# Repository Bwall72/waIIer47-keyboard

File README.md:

# WaIIer47 Mechanical Keyboard
Custom design 47 key ortholinear keyboard with PCB, and Atmega32u4 Microcontroller

## Images

Revision 2 Green, Revision 1 White, Back top, Front bottom

# Bill Of Materials

* See [BOM.md](./BOM.md)
* The total cost for a Rev 2 PCB keybarod is:

| Component | Unit Price | Units | Total |
| --------- | ---------- | ----- | ----- |
| Capacitor 22 pF | \$0.043  | 2 | \$0.086  |
| Capacitor 0.1 $\mu$F | \$0.0216  | 5 | \$0.108  |
| Capacitor 1.0 $\mu$F | \$0.055 | 1 | \$0.055 |
| Diode | \$.02446 | 47 | \$1.223 |
| LED | \$0.159 | 1 | \$0.159 |
| USB-C Receptacle | \$1.37 | 1 | \$1.37 |
| Kalih Speed Copper Key Switch | \$0.538 | 47 | \$25.286 |
| Resistor 10 k$\Omega$ | \$0.0071 | 2 | \$0.0142 |
| Resistor 22 $\Omega$ | \$0.0071 | 2 | \$0.0142 |
| Resistor 5.1 k$\Omega$ | \$0.0071 | 2 | \$0.0142 |
| Resistor 220 $\Omega$ | \$0.0071 | 1 | \$0.0071 |
| Push Button Switch | \$0.59 | 1 | \$0.59 |
| Atmega32U4 | \$4.08 | 1 | \$4.08 |
| Crystal Oscillator | \$0.36 | 1 | \$0.36 |
| PCB | \$2.08 | 2 | \$2.08 |
| M3 Screws | \$0.033 | 7 | \$0.233
| M3 Standoff | \$0.033 | 7 | \$0.233
| Total ||| \$35.89

>Notes
>
>* Shipping costs are excluded from the BOM
>* Currently, I am reusing keycaps, so those are not included in the BOM
>  * I am part of the group buy for [KAT Mizu Keycaps](https://old.reddit.com/r/mechmarket/comments/i6aaga/ic_kat_mizu_coming_september_1st/), which would add \$64.44 to the total
>* Kailh Speed Copper are my favorite switches, but they cannot be recomended for this keyboard. They are missing the pins to be used in a plateless keyboard like this one.

# PCB Tutorial
Designing a custom mechanical keyboard PCB using KiCad. The following was based on [Ruiqi Mao's Tutorial](https://github.com/ruiqimao/keyboard-pcb-guide)

## Download Kicad and Install the Mechanical Keyboard Libraries

* Download and install Kicad from https://kicad-pcb.org/
  * During installation, choose to download Kicad's default libraries
* Clone the following two repositories (or download zip and extract):
  * `keyboard_parts.pretty` from https://github.com/tmk/keyboard_parts.pretty
  * `keebs.pretty` from https://github.com/egladman/keebs.pretty
  * `Type-C.pretty` from https://github.com/ai03-2725/Type-C.pretty
  * `kicad_lib_tmk`.lib https://github.com/tmk/kicad_lib_tmk

* Open `Kicad` > `Preferences` > `Manage Footprint Libraries`
  * In the `Global Libraries` tab, press the folder icon to `Add existing library to table`
  * Navigate to where you cloned the the libraries, click on the `keebs.pretty` and press `OK`
    * Do the same for `keyboard_parts.pretty` and `Type-C.pretty`
  * If done successfully, you should see the following in the `Global Libraries` tab:

* Back in the Kicad Menu, `Preferences` > `Mange Symbol Libraries`
  * In the `Global Libraries` tab, press the folder icon to `Add existing library to table`
  * Navigate to where you cloned `kicad_lib_tmk` and select `keyboard_parts.lib`
  * Navigate to `Type-C.pretty` and select `Type-C.lib`
  * If done successfully, you should see the following:

## Creating The Schematic File

* In Kicad: `file` > `New` > `New Project`
  * Create a new Folder for the project, and give a name for the project (I am using `tutorial_keyboard`)
  * Press `Save`
  * On the left side, you should now see 3 files:
    * `tutorial_keyboard.kicad_pcb`: The PCB file
    * `tutorial_keyboard.pro`: The project file, we will not be using this
    * `tutorial_keyboard.sch`: The schematic file

* Click on the `Schematic Layout Editor` button
* Because this schematic will be large, increase the paper size by going to `file` > `Page Settings...` then selecting the `C` page size

## Placing Components on the Schematic

* To place a part, press the `Place symbol` button on the right side
* For the microcontroller:
  * `Place symbol` and click on the page > expand `keybord_parts` > select `ATMEGA32U4` > press `OK` > Click on the sheet to place the component
  * You should now see the component placed on your page with the label U?

* Place the following components as required by the [datasheet](http://ww1.microchip.com/downloads/en/devicedoc/atmel-7766-8-bit-avr-atmega16u4-32u4_datasheet.pdf)
  * A 10 k$\Omega$ resustor near `HWB/PE2`
    * `Place symbol` > `keyboard_parts` > `R` > `Ok`
      * Press `r` before placing the component, or while hovering over the component after placing to rotate it
      * Hover over it and press `e` to `Edit Value Field`
      * Change the `Text` field to say `10k`
    
  * A 1 $\mu$F capacitor on `UCap`
    * `place symbol` > `keyboard_parts` > `C` > `Ok`
    * Change the its value to `1uF`

* Connect `Vcc` and `GND`
  * On the right side, slect `Place power port` > click on the page
  * Expand the `power` library and select > `VCC` > `Ok`
  * Place the VCC flag near `AVCC`
    * On the right, click the `Place wire` icon
    * Click at the empty circle on `AVCC` and make a connection to the `VCC` flag
    
    * Repeat for:
      | Pin | Name   |
      |-----|--------|
      | 2   | `UVcc` |
      | 7   | `VBus` |
      | 14  | `VCC`  |
      | 24  | `AVcc` |
      | 34  | `VCC`  |
      | 44  | `AVcc` |
    * Make sure there are 6 total connections to `VCC`
    * Individual connections to `VCC` in the schematic do not need to be connected together
    * Connect `VCC` to a power flag
      * `Place symbol` > Search for `PWR_FLAG` > `PWR_FLAG`
      * Connect the `PWR_FLAG` to `VCC`
      
  * `Place power port` > `GND` (`Power flag, ground` from the `s`power` library)
    * Create a connection to `GND` on the following pins:
      | Pin | Name   |
      | --- | ------ |
      | 5   | `UGND` |
      | 15  | `GND`  |
      | 23  | `GND`  |
      | 35  | `GND`  |
      | 43  | `GND`  |
    * Additionally, connect the other end of the capacitor and resistor to `GND`
    * Make sure there are 5 connections to `GND`

* If there are any overlapping components or labels, press `m` over the component/label to move it somewhere else
  * You will have to remake any connections
* Reset Circuit
  * The following allows for a manual reset button that (If you do not want a reset button, connect `RESET` to `VCC`)
  * Move to an open part of the page
  * `Place symbol` > `keyboard_parts` > `SW_PUSH`
  * We want the voltage supplied to the reset pin to be `High (5V)` normally, and ground when pushed to reset the microcontroller
  * Connect the left side to `GND`
  * Create a connection between `VCC` -> 10 k$\Omega$ resistor -> switch-s right pin
  
  * Place a flag on the right side:
    * In the right menu: `Place net label`
    * Give it the name `Reset`
    * Connect it to the wire on the right side
    * Place a net label with the name `Reset` on the `RESET` pin (pin 13) of the microcontroller
    * The reset circuit is now connected to the microcontroller
    
* USB Type-C Circuit
  * This keyboard will connect to a computer using a USB-C connector in USB 2.0 Mode
  * `Place symbol` > `Connector` > `USB_C_Receptacle_USB2.0`
  * Make the following connections

  | Receptacle Port | Connection |
  | --------------- | ---------- |
  | `VBUS` | `VCC` |
  | `CC1` | 5.1 k$\Omega$ resistor -> `GND` |
  | `CC2` | 5.1 k$\Omega$ resistor -> `GND` |
  | `D-` | Connect both `D-` pins through a 22 $\Omega$  resistor to a net called `D-` |
  | `D+` | Connect both `D+` pins through a 22 $\Omega$ resistor to a net called `D+` |
  | `SBU1` | Leave unconnected |
  | `SBU2` | Leave unconnected |
  | `GND` | `GND` |
  | `SHIELD` | `GND` |
  
  * On the microcontroller, connect `D-` (pin 3) to the `D-` net and `D+` (pin 4) to the `D+` net

* Crystal Oscillator Circuit
  * The following circuit is required for the microcontroller to function as a USB device
  * `Place symbol` > `keyboard_parts` > `XTAL`
  * Connect a 22 pF capacitor to both ends of the `XTAL` with the other side going off to `GND`
  * Connect one side of the `XTAL` to a net called `xtal1` and the other to a net called `xtal2`
  * Connect the `xtal1` net to `XTAL1` (pin 16) and `xtal2` to `XTAL2` (pin 17) on the microcontroller

* Placing the keys
  * The following circuit is used for all the keys:
  
  * `Place symbol` > `keyboard_parts` > `KEYSW`
  * `Place symbol` > `keyboard_parts` > `D`
  * Connect the `2 pin` on the `KEYSW` on to the 2 pin on the diode **Orientation on the diode is extremely important**
  * For an 47 key ortholinear keyboard, copy and paste this circuit 46 times in rows of 12 (besides the third row which should have 11 keys)
  * Connect all the pin 1's on the switch on the same row
  * Connect all the pin 1's on the diode to the next pin 2 on the switch in the columns
  
  * Connect the bottom row diodes together
  
  * Create a net on the each of the vertical wire segments in the top row named `col0` to `col11`
  * Create a net on the the left most switch of each row labeled `row0` to `row3`

  * Connect each of the row and col nets to a GPIO pin on the microcontroller (`PAX`, `PBX`, `PCX`, or `PDX`) these can be changed later to make it easier to route the PCB
  
* Bypass Capacitors
  * Bypass capacitors are placed between all `VCC` nets and `GND`, watch this [video to learn more](https://www.youtube.com/watch?v=BcJ6UdDx1vg)
  * There are 6 connections that will use bypass capacitors
  * Create the following circuit using 0.1 $\mu$ capacitors
  
* Mark all unconnected ports
  * In the right menu, click `Place no connection flag`
  * Place the symbol over all unused ports on the microcontroller and on `SBU1` and `SBU2` on the USB C receptacle
  
* Annotate the schematic to give components names
  * `Tools` > `Annotate Schematic`
  * Keep all default settings
  * Press `Annotate`
  * `Close`
* Run a Design Rules Check to make sure there are no errors in the circuit
  * `Perform electrical rules check` > `Run`
  * Fix any errors that occur, if there are only errors for your `VCC` or `GND` not being driven, you can move on

## Assigning Footprints

* Assigning footprints tell the PCB software what size to make all of your components. Additionally you will buy components based off the size of their footprint. For most components we will use the `0805` surface mount package. If you do not feel comfortable surface mounting components, you will have to heavily modify the PCB layout.
* `Tools` > `Assign Footprints...`
  | Components | Library | Footprint |
  | ---------- | ------- | --------- |
  | All Capacitors | `Capacitor_SMD` | `Capacitor_SMD:C_0805_2012Metric` |
  | All Diodes | `Diode_SMD` | `Diode_SMD:D_0805_2012Metric` |
  | USB C Receptacle | `Type-C` | `Type-C:USB_C_GCT_USB4085` |
  | All `KEYSW` **EXCEPT FOR THE SPACE BAR** | `keebs` | `keebs:Mx_Alps_100` |
  | Space Bar (sixth key in on the bottom row) | `keebs` | `keebs:Mx_Alps_200` |
  | All Resistors | `Resistor_SMD` | `Resistor_SMD:R_0805_2012Metric` |
  | `SW_PUSH` | `Button_Switch_SMD` | `Button_Switch_SMD:SW_SPST_TL3342` |
  | `ATMEGA32U4` | `Package_QFP` | `Package_QFP:TQFP-44_10x10mm_P0.8mm` |
  | `XTAL` | `keyboard_parts` | `keyboard_parts:XTAL_HC_49_TH`

  * Press `OK`

## Creating the PCB

### Set the Grid Size

* Click the `Grid` dropdown menu on the top
* `Edit User Grid`
* Set `Size X` and `Size Y` to `0.254`

### Importing From the Schematic

* Close the schematic and open `PCB Layout Editor`
* `Tools` > `Update PCB from Schematic`
* Click Anywhere to Place all the components
* Click `Layers Manager` > `Items` > Uncheck the box next to `Ratsnest`
  * This will be helpful when routing the PCB, but it is not now

### Organizing your components

* Arrange the keys in the same order as your circuit
* The easiest way I found to do this is to use `ctrl + f` to search for the key annotations
* I like to leave one _grid snap_ gap between each key, make sure all keys are evenly spaced on the grid
* There should be a visible `+` sign between all groups for 4 adjacent keys

> Follow the annotations from your schematic to put the keys in the correct order

### Place the Other Parts

* Because this keyboard mostly uses surface mount components, they will mostly go on the back to hide them
* To place a component on the back, click on the footprint and press `f`
  * The text for the label should be backwards and in purple
* Flip all diodes to the back, and align them onto their key switch
* Place the diode on the lower part of the key switch (opposite of the gold)

* Turning on `ratsnest` may be helpful for this part
* Arrange the other parts on the back above the key switches
  * All the components in the schematic that are near the microcontroller should go near the microcontroller
  * 5 bypass capacitors should go near the microcontroller with the other going near the USB-C receptacle
* The crystal should go on the back as close as possible to the microcontroller pins it connects to
* The Type-C connector should go on the front, it will be the highest component on the PCB
* The switch can go on the front or back based on preference, I put it on the front

### Adjust your circuit

* With the `ratsnest` turned on, move the location of rows and cols on your microcontroller to reduce the number of ratsnests that overlap
* After making a change, `Tools` > `Update PCB From Schematic`

### Set the Track Width

* I use [JLCPCB](https://jlcpcb.com/) to manufacture my PCBs, their minimum trace width is 5 mil (0.127 mm) with the same minimum spacing

* The default .254 mm width does not need to be changed, but you can go down to .2 mm to have smaller traces

### Making connections

* To make a connection, use the bar on the right to select a layer
  * `F.CU` for components on the front
  * `B.CU` for components on the back
* You must select the layer of the starting component to make a connection
* With the correct layer selected, press `Route tracks`
* Connect all components, but do not connect any `GND` nets, those will all be taken care of in the end

* To make connections easier, click on the footprint and press `R` to rotate the component if that makes it easier
* I recommend breaking out all the pins of the microcontroller before worrying about connecting the microcontroller to components
* If traces are going to overlap, press `v` to insert a `via` between the front and the back to switch layers

### Create the Remaining Connections

Connect the diodes for all keys in the same row

Connect the switches in the same column

Break out connections from the USB-C receptacle

### Add Mounting Holes

* This desing suspends the PCB from standoffs, to use them, m3 screw holes are added to the PCB
* `Place` > `Footprint` > `MountingHole_3.2mm_M3`
* I personally put 3 screw holes on each side and one in the middle
  * Adding more holes can make the PCB flex less

### Creating an outline for the PCB

* Select the `Edge.Cuts` layer
* Select the `Add graphic lines` tool
* Draw a **fully connected** rectangle around all your components
* The USB-C connector should be on the outer limits of the PCB on the top, and the screw holes should be the limit on the sides
* The smaller the PCB, the cheeper it will be to fabricate

* After creating the outline, try opening `View` > `3D Viewer`
* If you see the folowing error, look for any missing connections in your edge cuts or extra lines

* Once you fix all the errors, you should be able to view a 3D rendering of the PCB

### Adding a Ground Plane

* In the previous steps, no connections were made to ground, we will resolve them all now
* On the right side, select the `Add filled zones` tool on the back side and the `GND` net

* Select the top left corner > top right corner > bottom right corner > **double click on the lower left corner**
* You should see:

* By zooming in, you can see connections made to ground nets

* Repeat the process on the top side

> Press the `Do not show filled zones` button on the left side to hide the filled zones

### Run the Design Rules Check

* Press `Perform Design Rules Check` on the top bar
* Select the `Refill all zones before running DRC` > `Run DRC`
* Resolve any errors that show up
* The most common errors are:
  * Missing connections to ground:
    * It is possible that your filled zones cannot get around a trace or component, you may need to add some manual ground connections
  * Traces too close:
    * Re-route the traces to increase the distance between the traces
  * Traces too close to holes in PCB
    * Move the trace
* When there are no design rule check violations, the PCB is complete

## Submitting PCB for Fabrication

### Generate Gerber Files

* [Refer to this page from JLCPCB for instructions](https://support.jlcpcb.com/article/44-how-to-export-kicad-pcb-to-gerber-files)
* `File` > `Plot`
* Select a folder for `Output Directory`
* On the front page, leave all the default settings and press `Plot`
* Press `Generate Drill Files...`
  * Click the `Gerber` option on the left
  * Press `Generate Drill File`

### Submitting to JLCPCB
(Instructions will also be shown for [OSHPARK](https://oshpark.com/), but they are much more expensive for large PCBs)

* Create a `.zip` from the output folder
* Go to [JLCPCB](www.jlcpcb.com)
* Press `QUOTE NOW`
* `Add your gerber file` > Select your `.zip`
* You can leave all the default options unless you want a different color
* Proceeded with checkout, they will verify your that your design complies with their manufacturing process and has all the needed files
* \$10.40 + 16 for Fedex Shipping
* Total time to receive your PCB should be less than two weeks (unless shipping by boat)

### OSHPARK

* PCBs from OSHPARK are more expensive, but higher quality. For large runs, it may make sense to use OSHPARK (you also have to be fine with a purple PCB)
* Go to [wwww.oshpark.com](www.oshpark.com)
* Upload your `.zip`
* I saw that their quote was 5 times as much for 2 fiewer PCBs and did not continue...

# Ordering Components from Digikey

* For this tutorial, the following components are purchased from [Digikey](www.digikey.com)
* Note the quantities needed per the schematic and **BUY MORE THAN YOU NEED**, **A LOT MORE** (I generally buy 5-10 times as many of each component, it is often cheaper to buy at higher quantities)

| Item # | Item | Price | Digikey Link | Data Sheet |
| ------ | ---- | ------| --------| ---------- |
1 | USB C Connector | \$1.37 | [Link](https://www.digikey.com/product-detail/en/gct/USB4085-GF-A/2073-USB4085-GF-ACT-ND/9859733) | [Link](https://media.digikey.com/pdf/Data%20Sheets/GCT%20PDFs/Ionex_USB_Conn_Br.pdf)
2 | Capacitor (22pF) | \$0.043 | [Link](https://www.digikey.com/product-detail/en/w%C3%BCrth-elektronik/885012007012/732-7816-1-ND/5454443) | [Link](https://www.we-online.de/katalog/datasheet/885012007012.pdf)
3 | Capacitor (0.1 $\mu$F) | \$0.0216 | [Link](https://www.digikey.com/product-detail/en/samsung-electro-mechanics/CL21B104KACNNNC/1276-1099-1-ND/3889185) | [Link](https://media.digikey.com/pdf/Data%20Sheets/Samsung%20PDFs/CL21B104KACNNNC_Spec.pdf)
4 | Capacitor (1 $\mu$F) | \$0.055 | [Link](https://www.digikey.com/product-detail/en/samsung-electro-mechanics/CL21B105KOFNNNE/1276-1026-1-ND/3889112) | [Link](https://www.datasheets360.com/pdf/5320303544541785574)
5 | Diode | \$.02446 | [Link](https://www.digikey.com/product-detail/en/nexperia-usa-inc/BAS16GWJ/1727-7320-1-ND/7390571) | [Link](https://assets.nexperia.com/documents/data-sheet/BAS16GW.pdf)
6 | Resistor (10 k$\Omega$) | $0.0071 | [Link](https://www.digikey.com/product-detail/en/stackpole-electronics-inc/RMCF0805JT10K0/RMCF0805JT10K0CT-ND/1942577) | [Link](https://www.seielect.com/catalog/sei-rmcf_rmcp.pdf)
7 | Resistor (22 $\Omega$) | $0.0071 | [Link](https://www.digikey.com/product-detail/en/stackpole-electronics-inc/RMCF0805JT22R0/RMCF0805JT22R0CT-ND/1942533) | [Link](https://www.seielect.com/catalog/sei-rmcf_rmcp.pdf)
8 | Resistor (5.1 k$\Omega$) | $0.0071 | [Link](https://www.digikey.com/product-detail/en/stackpole-electronics-inc/RMCF0805JT5K10/RMCF0805JT5K10CT-ND/1942571) | [Link](https://www.seielect.com/catalog/sei-rmcf_rmcp.pdf)
9 | Switch | $0.59 | [Link](https://www.digikey.com/product-detail/en/e-switch/TL3342F160QG-TR/EG2531CT-ND/379004) | [Link](https://sten-eswitch-13110800-production.s3.amazonaws.com/system/asset/product_line/data_sheet/165/TL3342.pdf)

* To search on your own for components (resistor example):
  * Go to [Digikey](https://www.digikey.com/)
  * `Products` > `Passives` > `Resistors` > `Chip Resistor - Surface Mount`
  * Use the filters to get the correct value resistor
  * Set the `View Prices At` value to 10
    * For most components, I ended up in the 10-100 piece price bracket
    * This will exclude any components that can only be purchased in high quantities
    * Click `More Filters`
    * `Package` > `0805` (based on the assigned footprint)
    * `Apply All`
    * I also recommend deselecting `Include` under `Marketplace Product`
  * `Applied Filters` should show `Package/Case` and `Resistance`

  * In the table, click the `Search Ascending` arrow under `Price` to show the lowest cost components
    * For this keyboard, there really aren't any components where using a more expensive part is worth getting

* Repeat this process for all the other components, or use the products I listed in the table

## Components From Other Sources

* I already owned the crystal oscillators, which is why I use through hole for them
  * [Amazon - uxcell 16.00 MHz crystal oscillator](https://smile.amazon.com/a14073000ux0239-Profile-Crystal-Oscillator-Replacements/dp/B00SWK2HCO)
* [Amazon - Brass M3 Screw and Standoff Kit](https://smile.amazon.com/Csdtylh-Male-Female-Standoff-Stainless-Assortment/dp/B06Y5TJXY1)

### Keyswitches

* I recommend ordering keyswitches from [Mechanicalkeyboards.com](https://mechanicalkeyboards.com/shop/index.php?l=product_list&c=107)
* **MAKE SURE THE SWITCHES YOU CHOOSE SAY PCB MOUNT**
  * I used my favorite switch, Kalih Speed Copper, which is plate mount
  * PCB mounted switches have two additional feet to help alignment
  * Plate mounted switches are very hard to align
  * Do not buy plate mounted switches

**WIP**

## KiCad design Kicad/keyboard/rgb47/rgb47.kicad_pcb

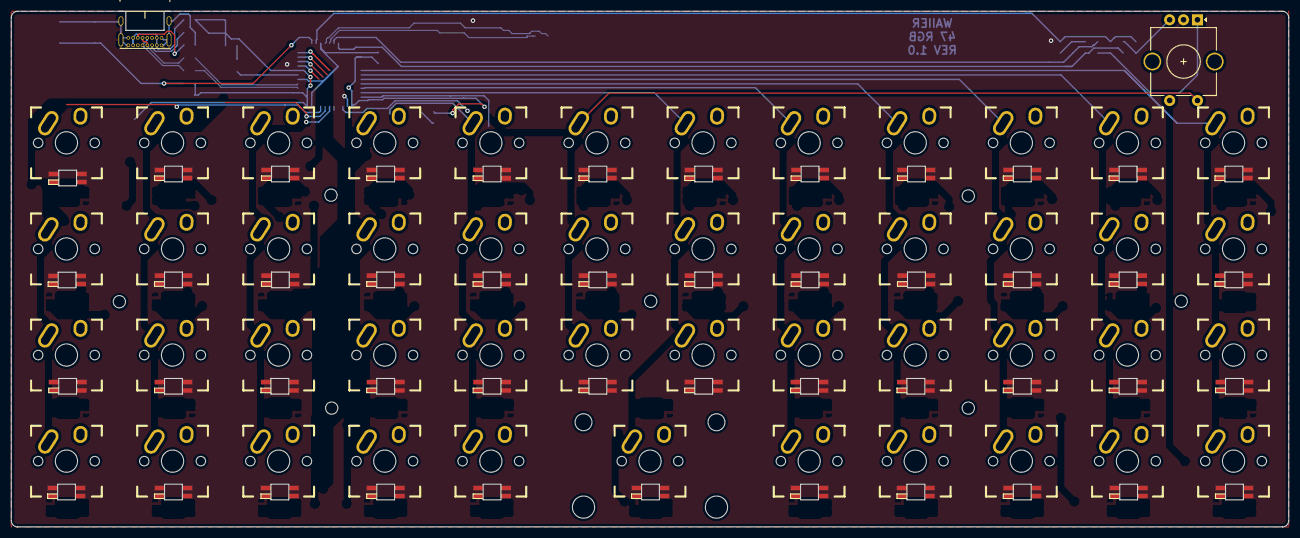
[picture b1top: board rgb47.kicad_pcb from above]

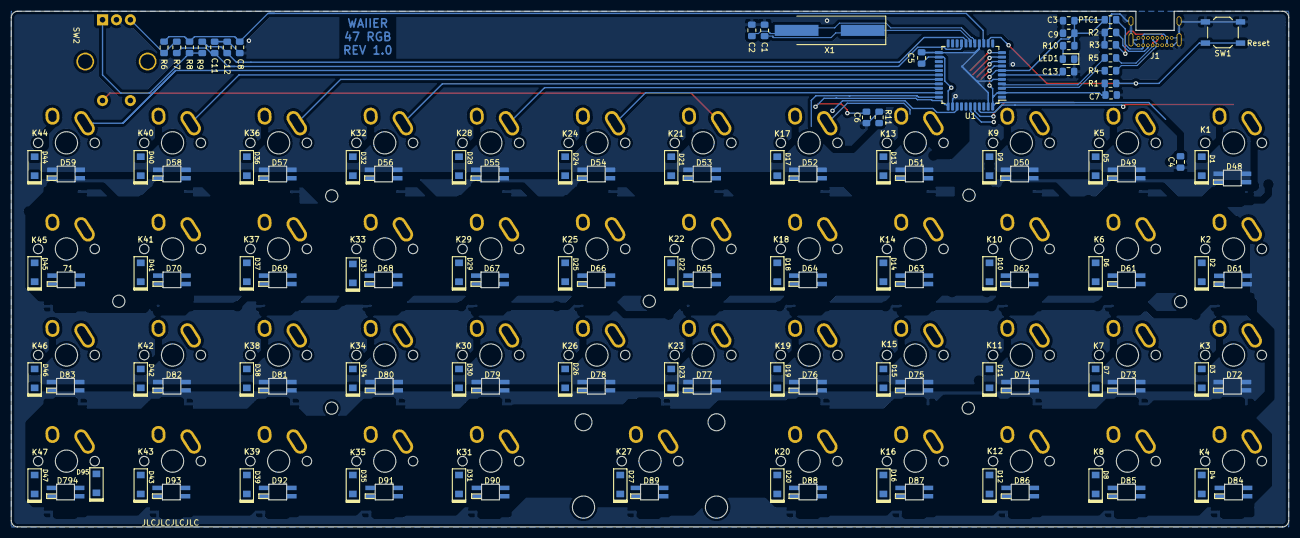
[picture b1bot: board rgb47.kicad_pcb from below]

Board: 2 copper layers, 229.4 x 92.6 mm, 172 parts (76 on the bottom side), 129 nets.

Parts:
71: SK6812; sk6812_mini_E_cuts
C1, C2: 22p; C_0805_2012Metric_Pad1.15x1.40mm_HandSolder
C3, C4, C5, C6, C7, C8, C11, C12: 0.1u; C_0805_2012Metric_Pad1.15x1.40mm_HandSolder
C9: 10u; C_0805_2012Metric_Pad1.15x1.40mm_HandSolder
C13: 1u; C_0805_2012Metric_Pad1.15x1.40mm_HandSolder
D1, D2, D3, D4, D5, D6, D7, D8, D9, D10, D11, D12, D13, D14, D15, D16, D17, D18, D19, D20, D21, D22, D23, D24, D25, D26, D27, D28, D29, D30, D31, D32, D33, D34, D35, D36, D37, D38, D39, D40, D41, D42, D43, D44, D45, D46, D47, D95: D; D_SOD123
D48, D49, D50, D51, D52, D53, D54, D55, D56, D57, D58, D59, D61, D61#2, D62, D63, D64, D65, D66, D67, D68, D69, D70, D72, D73, D74, D75, D76, D77, D78, D79, D80, D81, D82, D83, D84, D85, D86, D87, D88, D89, D90, D91, D92, D93, D794: SK6812; sk6812_mini_E_cuts
J1: USB_C_Receptacle_USB2.0; USB_C_GCT_USB4085
K1, K2, K3, K4, K5, K6, K7, K8, K9, K10, K11, K12, K13, K14, K15, K16, K17, K18, K19, K20, K21, K22, K23, K24, K25, K26, K28, K29, K30, K31, K32, K33, K34, K35, K36, K37, K38, K39, K40, K41, K42, K43, K44, K45, K46, K47: KEYSW; Mx_Alps_100
K27: KEYSW; Mx_Alps_200
LED1: LED; LED_0805_2012Metric_Pad1.15x1.40mm_HandSolder
PTC1: PTC 1.5A; Fuse_0805_2012Metric_Pad1.15x1.40mm_HandSolder
R1, R6, R7, R8, R9, R11: 10k; R_0805_2012Metric_Pad1.15x1.40mm_HandSolder
R2, R3: 5.1k; R_0805_2012Metric_Pad1.15x1.40mm_HandSolder
R4, R5: 22; R_0805_2012Metric_Pad1.15x1.40mm_HandSolder
R10: 220; R_0805_2012Metric_Pad1.15x1.40mm_HandSolder
SW1: SW_PUSH; SW_SPST_TL3342
SW2: Rotary_Encoder_Switch; RotaryEncoder_Alps_EC11E-Switch_Vertical_H20mm_CircularMoun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
U1: ATMEGA32U4; LQFP-44_10x10mm_P0.8mm
X1: XTAL; Crystal_SMD_HC49-SD_HandSoldering

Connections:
5V: 71.3, C3.2, C4.2, C5.2, C6.2, C7.2, C8.2, C9.2, D48.3, D49.3, D50.3, D51.3, D52.3, D53.3, D54.3, D55.3, D56.3, D57.3, D58.3, D59.3, D61.3, D61#2.3, D62.3, D63.3, D64.3, D65.3, D66.3, D67.3, D68.3, D69.3, D70.3, D72.3, D73.3, D74.3, D75.3, D76.3, D77.3, D78.3, D79.3, D80.3, D81.3, D82.3, D83.3, D84.3, D85.3, D86.3, D87.3, D88.3, D89.3, D90.3, D91.3, D92.3, D93.3, D794.1, PTC1.2, R1.1, R6.2, R8.2, R10.1, U1.2, U1.7, U1.14, U1.24, U1.34, U1.44
/COL0: K1.1, K2.1, K3.1, K4.1, U1.41
/COL1: K5.1, K6.1, K7.1, K8.1, U1.40
/COL2: K9.1, K10.1, K11.1, K12.1, U1.39
/COL3: K13.1, K14.1, K15.1, K16.1, U1.38
/COL4: K17.1, K18.1, K19.1, K20.1, U1.37
/COL5: K21.1, K22.1, K23.1, SW2.S2, U1.36
/COL6: K24.1, K25.1, K26.1, K27.1, U1.32
/COL7: K28.1, K29.1, K30.1, K31.1, U1.31
/COL8: K32.1, K33.1, K34.1, K35.1, U1.30
/COL9: K36.1, K37.1, K38.1, K39.1, U1.29
/COL10: K40.1, K41.1, K42.1, K43.1, U1.28
/COL11: K44.1, K45.1, K46.1, K47.1, U1.27
/D+: R5.1, U1.4
/D-: R4.1, U1.3
/ENCODER_A: R8.1, R9.2, SW2.A
/ENCODER_AOUT: C12.2, R9.1, U1.18
/ENCODER_B: R6.1, R7.2, SW2.B
/ENCODER_BOUT: C11.2, R7.1, U1.19
/ENCODER_S1: D95.2, SW2.S1
/RESET: R1.2, SW1.1, U1.13
/RGB: D48.2, U1.1
/ROW0: D1.1, D5.1, D9.1, D13.1, D17.1, D21.1, D24.1, D28.1, D32.1, D36.1, D40.1, D44.1, U1.8
/ROW1: D2.1, D6.1, D10.1, D14.1, D18.1, D22.1, D25.1, D29.1, D33.1, D37.1, D41.1, D45.1, U1.9
/ROW2: D3.1, D7.1, D11.1, D15.1, D19.1, D23.1, D26.1, D30.1, D34.1, D38.1, D42.1, D46.1, U1.10
/ROW3: D4.1, D8.1, D12.1, D16.1, D20.1, D27.1, D31.1, D35.1, D39.1, D43.1, D47.1, D95.1, U1.11
/XTAL_N: C2.2, U1.16, X1.2
/XTAL_P: C1.2, U1.17, X1.1
GND: 71.1, C1.1, C2.1, C3.1, C4.1, C5.1, C6.1, C7.1, C8.1, C9.1, C11.1, C12.1, C13.2, D48.1, D49.1, D50.1, D51.1, D52.1, D53.1, D54.1, D55.1, D56.1, D57.1, D58.1, D59.1, D61.1, D61#2.1, D62.1, D63.1, D64.1, D65.1, D66.1, D67.1, D68.1, D69.1, D70.1, D72.1, D73.1, D74.1, D75.1, D76.1, D77.1, D78.1, D79.1, D80.1, D81.1, D82.1, D83.1, D84.1, D85.1, D86.1, D87.1, D88.1, D89.1, D90.1, D91.1, D92.1, D93.1, D794.3, J1.A1, J1.A12, J1.B1, J1.B12, J1.S1, LED1.1, R2.1, R3.1, R11.1, SW1.2, SW2.C, U1.5, U1.15, U1.23, U1.35, U1.43
unnamed: C13.1, U1.6
unnamed: D1.2, K1.2
unnamed: D2.2, K2.2
unnamed: D3.2, K3.2
unnamed: D4.2, K4.2
unnamed: D5.2, K5.2
unnamed: D6.2, K6.2
unnamed: D7.2, K7.2
unnamed: D8.2, K8.2
unnamed: D9.2, K9.2
unnamed: D10.2, K10.2
unnamed: D11.2, K11.2
unnamed: D12.2, K12.2
unnamed: D13.2, K13.2
unnamed: D14.2, K14.2
unnamed: D15.2, K15.2
unnamed: D16.2, K16.2
unnamed: D17.2, K17.2
unnamed: D18.2, K18.2
unnamed: D19.2, K19.2
unnamed: D20.2, K20.2
unnamed: D21.2, K21.2
unnamed: D22.2, K22.2
unnamed: D23.2, K23.2
unnamed: D24.2, K24.2
unnamed: D25.2, K25.2
unnamed: D26.2, K26.2
unnamed: D27.2, K27.2
unnamed: D28.2, K28.2
unnamed: D29.2, K29.2
unnamed: D30.2, K30.2
unnamed: D31.2, K31.2
unnamed: D32.2, K32.2
unnamed: D33.2, K33.2
unnamed: D34.2, K34.2
unnamed: D35.2, K35.2
unnamed: D36.2, K36.2
unnamed: D37.2, K37.2
unnamed: D38.2, K38.2
unnamed: D39.2, K39.2
unnamed: D40.2, K40.2
unnamed: D41.2, K41.2
unnamed: D42.2, K42.2
unnamed: D43.2, K43.2
unnamed: D44.2, K44.2
unnamed: D45.2, K45.2
unnamed: D46.2, K46.2
unnamed: D47.2, K47.2
unnamed: D48.4, D49.2
unnamed: D49.4, D50.2
unnamed: D50.4, D93.2
unnamed: D51.2, D93.4
unnamed: D51.4, D52.2
unnamed: D52.4, D53.2
unnamed: D53.4, D54.2
unnamed: D54.4, D55.2
unnamed: D55.4, D56.2
unnamed: D56.4, D57.2
unnamed: D57.4, D58.2
unnamed: D58.4, D70.2
unnamed: D59.2, D61.4
unnamed: 71.2, D59.4
unnamed: D61.2, D61#2.4
unnamed: D61#2.2, D62.4
unnamed: D62.2, D63.4
unnamed: D63.2, D64.4
unnamed: D64.2, D65.4
unnamed: D65.2, D66.4
unnamed: D66.2, D67.4
unnamed: D67.2, D68.4
unnamed: D68.2, D69.4
unnamed: D69.2, D70.4
unnamed: 71.4, D72.2
unnamed: D72.4, D73.2
unnamed: D73.4, D74.2
unnamed: D74.4, D794.4
unnamed: D75.2, D794.2
unnamed: D75.4, D76.2
unnamed: D76.4, D77.2
unnamed: D77.4, D78.2
unnamed: D78.4, D79.2
unnamed: D79.4, D80.2
unnamed: D80.4, D81.2
unnamed: D82.2, D83.4
unnamed: D83.2, D84.4
unnamed: D84.2, D85.4
unnamed: D85.2, D86.4
unnamed: D86.2, D87.4
unnamed: D87.2, D88.4
unnamed: D88.2, D89.4
unnamed: D89.2, D90.4
unnamed: D90.2, D91.4
unnamed: D91.2, D92.4
unnamed: J1.A5, R2.2
unnamed: J1.A6, J1.B6, R5.2
unnamed: J1.A7, J1.B7, R4.2
unnamed: J1.B5, R3.2
unnamed: LED1.2, R10.2
unnamed: R11.2, U1.33
VCC: J1.A4, J1.A9, J1.B4, J1.B9, PTC1.1

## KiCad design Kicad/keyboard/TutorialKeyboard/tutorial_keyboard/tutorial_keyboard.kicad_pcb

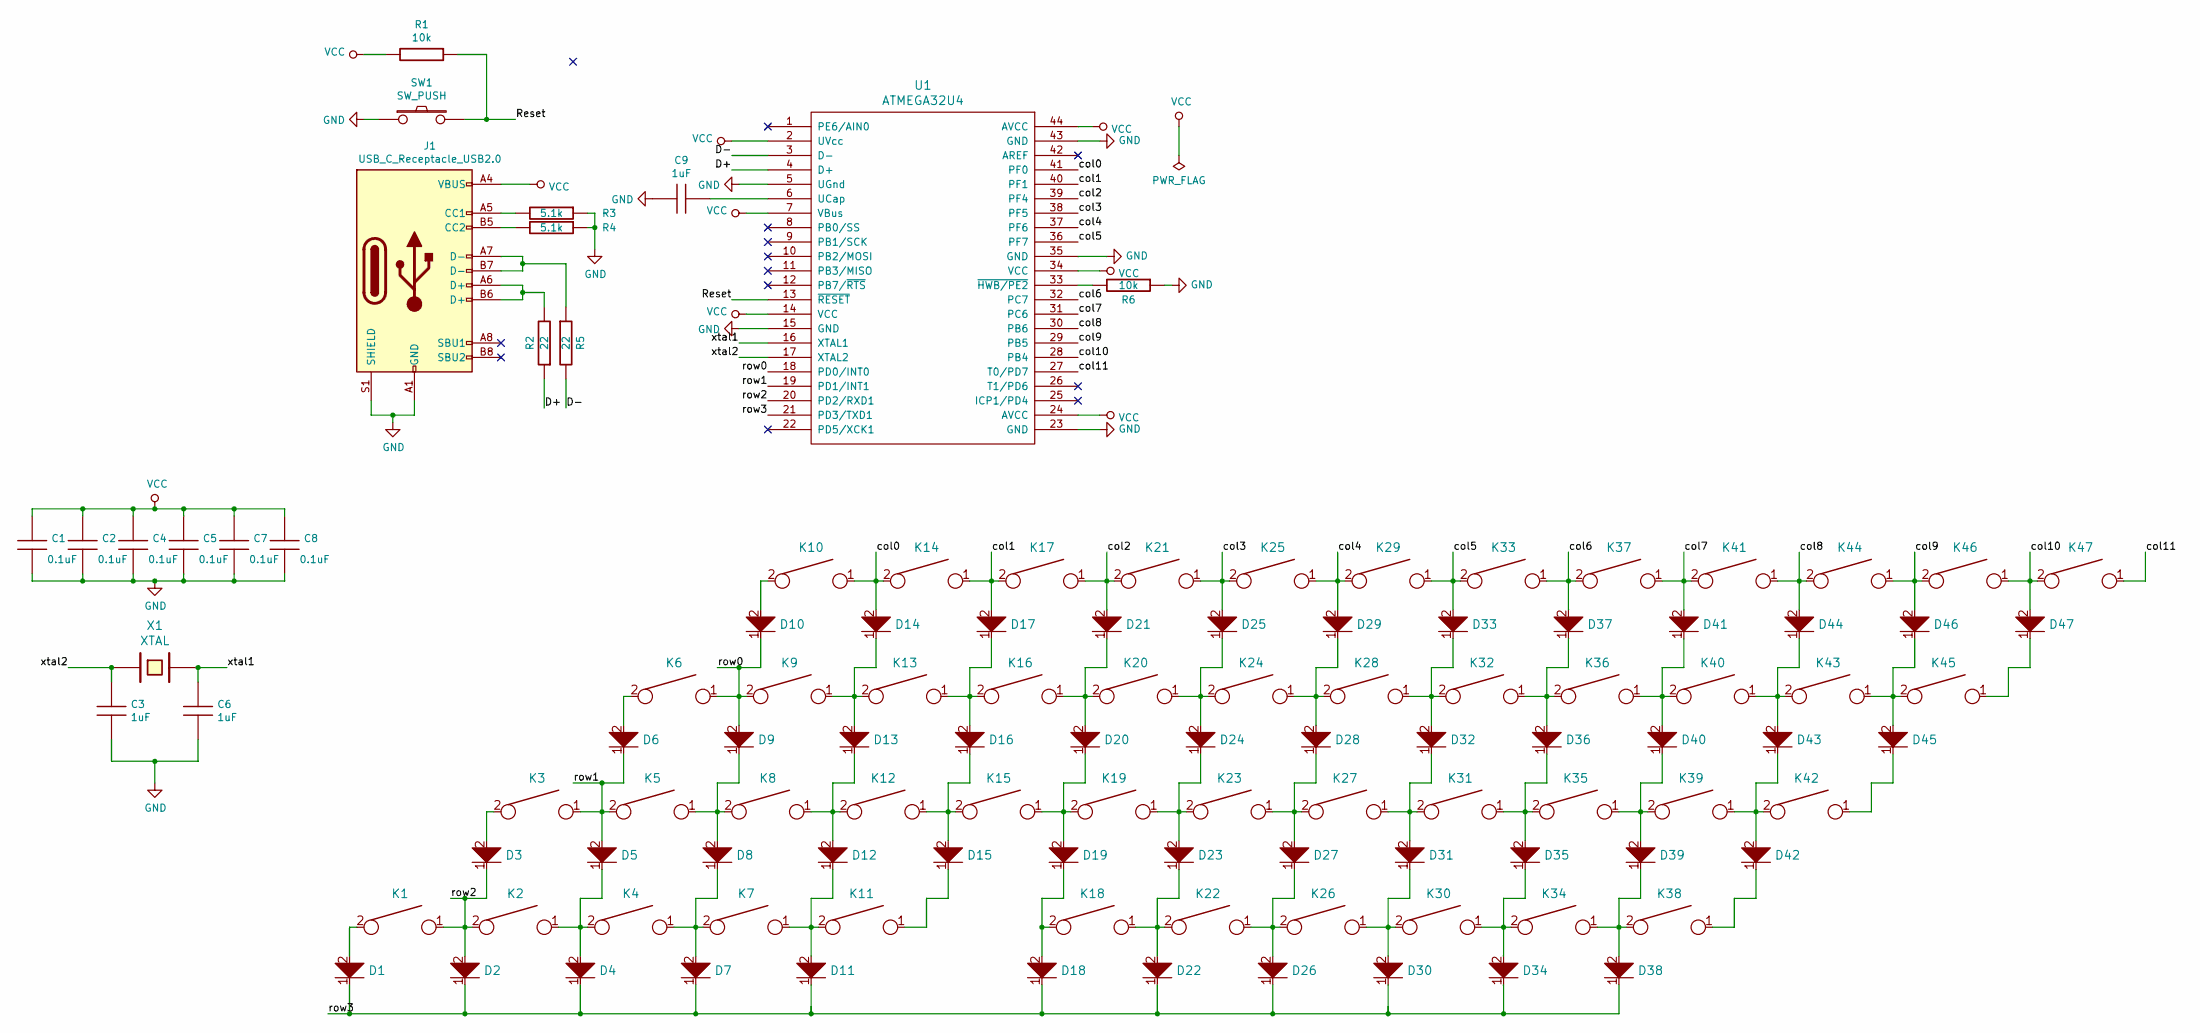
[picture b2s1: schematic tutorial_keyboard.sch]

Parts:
C1, C2, C4, C5, C7, C8: 0.1uF; C_0805_2012Metric
C3, C6, C9: 1uF; C_0805_2012Metric
D1, D2, D3, D4, D5, D6, D7, D8, D9, D10, D11, D12, D13, D14, D15, D16, D17, D18, D19, D20, D21, D22, D23, D24, D25, D26, D27, D28, D29, D30, D31, D32, D33, D34, D35, D36, D37, D38, D39, D40, D41, D42, D43, D44, D45, D46, D47: D; D_0805_2012Metric
J1: USB_C_Receptacle_USB2.0; USB_C_GCT_USB4085
K1, K2, K3, K4, K5, K6, K7, K8, K9, K10, K11, K12, K13, K14, K15, K16, K17, K19, K20, K21, K22, K23, K24, K25, K26, K27, K28, K29, K30, K31, K32, K33, K34, K35, K36, K37, K38, K39, K40, K41, K42, K43, K44, K45, K46, K47: KEYSW; Mx_Alps_100
K18: KEYSW; Mx_Alps_200
R1, R6: 10k; R_0805_2012Metric
R2, R5: 22; R_0805_2012Metric
R3, R4: 5.1k; R_0805_2012Metric
SW1: SW_PUSH; SW_SPST_TL3342
U1: ATMEGA32U4; LQFP-44_10x10mm_P0.8mm
X1: XTAL; XTAL_HC_49_TH

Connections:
/D+: R2.1, U1.4 (D+)
/D-: R5.2, U1.3 (D-)
/Reset: R1.1, SW1.2, U1.13 (~RESET)
/col0: D14.2, K10.1, K14.2, U1.41 (PF0)
/col1: D17.2, K14.1, K17.2, U1.40 (PF1)
/col2: D21.2, K17.1, K21.2, U1.39 (PF4)
/col3: D25.2, K21.1, K25.2, U1.38 (PF5)
/col4: D29.2, K25.1, K29.2, U1.37 (PF6)
/col5: D33.2, K29.1, K33.2, U1.36 (PF7)
/col6: D37.2, K33.1, K37.2, U1.32 (PC7)
/col7: D41.2, K37.1, K41.2, U1.31 (PC6)
/col8: D44.2, K41.1, K44.2, U1.30 (PB6)
/col9: D46.2, K44.1, K46.2, U1.29 (PB5)
/col10: D47.2, K46.1, K47.2, U1.28 (PB4)
/col11: K47.1, U1.27 (T0/PD7)
/row0: D9.2, D10.1, K6.1, K9.2, U1.18 (PD0/INT0)
/row1: D5.2, D6.1, K3.1, K5.2, U1.19 (PD1/INT1)
/row2: D2.2, D3.1, K1.1, K2.2, U1.20 (PD2/RXD1)
/row3: D1.1, D2.1, D4.1, D7.1, D11.1, D18.1, D22.1, D26.1, D30.1, D34.1, D38.1, U1.21 (PD3/TXD1)
/xtal1: C6.2, U1.16 (XTAL1), X1.2
/xtal2: C3.2, U1.17 (XTAL2), X1.1
GND: C1.1, C2.1, C3.1, C4.1, C5.1, C6.1, C7.1, C8.1, C9.2, J1.A1 (GND), J1.A12 (GND), J1.B1 (GND), J1.B12 (GND), J1.S1 (SHIELD), R3.1, R4.1, R6.1, SW1.1, U1.5 (UGnd), U1.15 (GND), U1.23 (GND), U1.35 (GND), U1.43 (GND)
unnamed: C9.1, U1.6 (UCap)
unnamed: D1.2, K1.2
unnamed: D3.2, K3.2
unnamed: D4.2, D5.1, K2.1, K4.2
unnamed: D6.2, K6.2
unnamed: D7.2, D8.1, K4.1, K7.2
unnamed: D8.2, D9.1, K5.1, K8.2
unnamed: D10.2, K10.2
unnamed: D11.2, D12.1, K7.1, K11.2
unnamed: D12.2, D13.1, K8.1, K12.2
unnamed: D13.2, D14.1, K9.1, K13.2
unnamed: D15.1, K11.1
unnamed: D15.2, D16.1, K12.1, K15.2
unnamed: D16.2, D17.1, K13.1, K16.2
unnamed: D18.2, D19.1, K18.2
unnamed: D19.2, D20.1, K15.1, K19.2
unnamed: D20.2, D21.1, K16.1, K20.2
unnamed: D22.2, D23.1, K18.1, K22.2
unnamed: D23.2, D24.1, K19.1, K23.2
unnamed: D24.2, D25.1, K20.1, K24.2
unnamed: D26.2, D27.1, K22.1, K26.2
unnamed: D27.2, D28.1, K23.1, K27.2
unnamed: D28.2, D29.1, K24.1, K28.2
unnamed: D30.2, D31.1, K26.1, K30.2
unnamed: D31.2, D32.1, K27.1, K31.2
unnamed: D32.2, D33.1, K28.1, K32.2
unnamed: D34.2, D35.1, K30.1, K34.2
unnamed: D35.2, D36.1, K31.1, K35.2
unnamed: D36.2, D37.1, K32.1, K36.2
unnamed: D38.2, D39.1, K34.1, K38.2
unnamed: D39.2, D40.1, K35.1, K39.2
unnamed: D40.2, D41.1, K36.1, K40.2
unnamed: D42.1, K38.1
unnamed: D42.2, D43.1, K39.1, K42.2
unnamed: D43.2, D44.1, K40.1, K43.2
unnamed: D45.1, K42.1
unnamed: D45.2, D46.1, K43.1, K45.2
unnamed: D47.1, K45.1
unnamed: J1.A5 (CC1), R3.2
unnamed: J1.A6 (D+), J1.B6 (D+), R2.2
unnamed: J1.A7 (D-), J1.B7 (D-), R5.1
unnamed: J1.B5 (CC2), R4.2
unnamed: R6.2, U1.33 (~HWB/PE2)
VCC: C1.2, C2.2, C4.2, C5.2, C7.2, C8.2, J1.A4 (VBUS), J1.A9 (VBUS), J1.B4 (VBUS), J1.B9 (VBUS), R1.2, U1.2 (UVcc), U1.7 (VBus), U1.14 (VCC), U1.24 (AVCC), U1.34 (VCC), U1.44 (AVCC)

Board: 2 copper layers, 113 parts (0 on the bottom side), 66 nets, no tracks yet.

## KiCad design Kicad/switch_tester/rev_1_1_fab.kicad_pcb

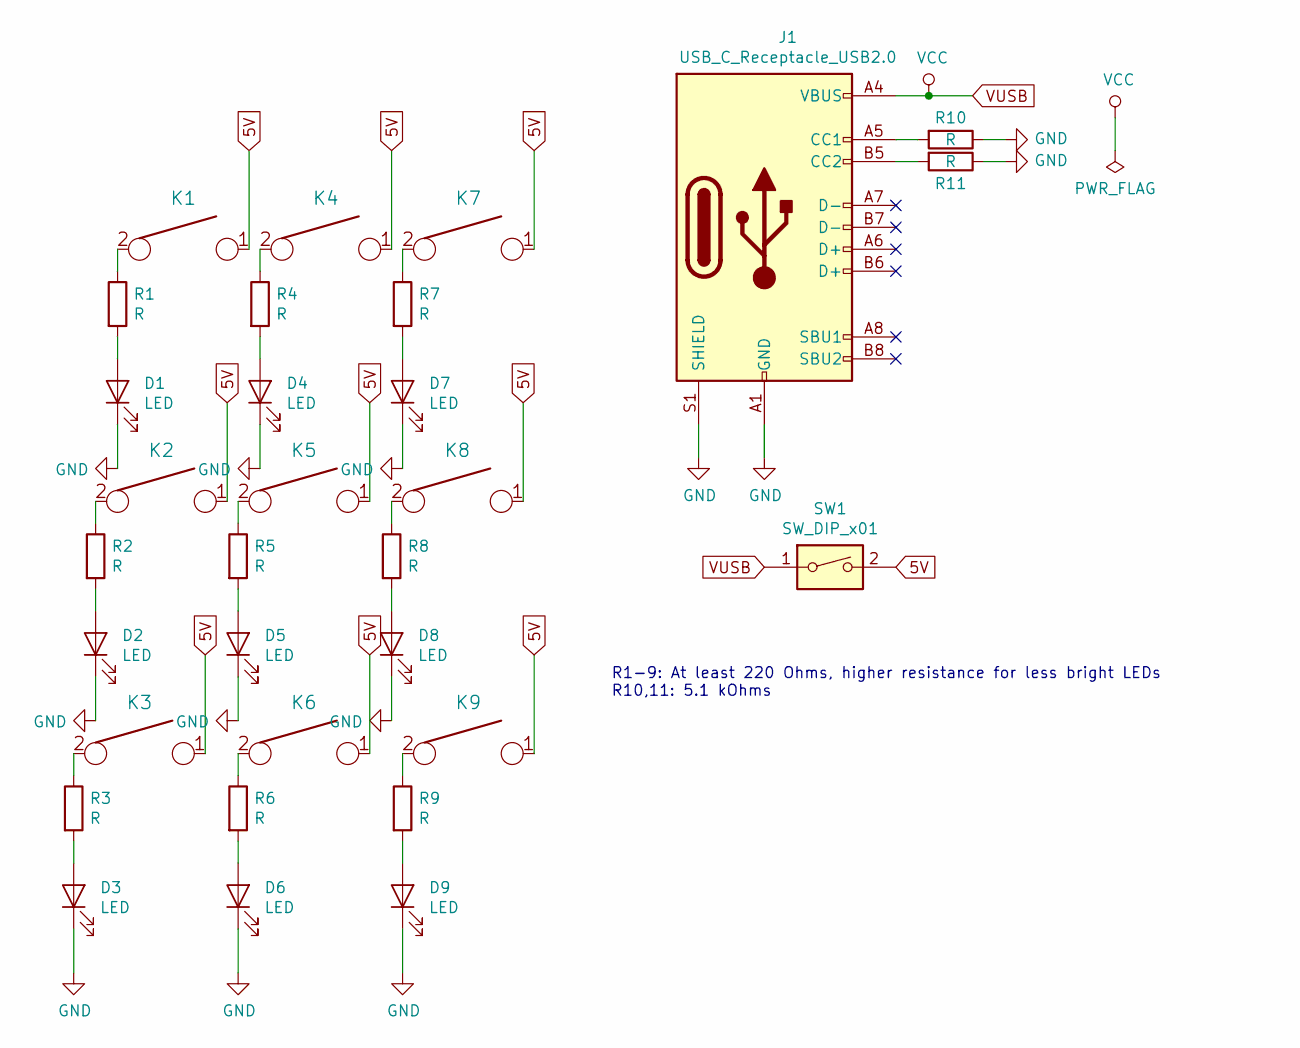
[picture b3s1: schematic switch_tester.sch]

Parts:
D1, D2, D3, D4, D5, D6, D7, D8, D9: LED; LED_D5.0mm
J1: USB_C_Receptacle_USB2.0; USB_C_GCT_USB4085
K1, K2, K3, K4, K5, K6, K7, K8, K9: KEYSW; Kailh_socket_MX_optional
R1, R2, R3, R4, R5, R6, R7, R8, R9, R10, R11: R; R_Axial_DIN0207_L6.3mm_D2.5mm_P7.62mm_Horizontal
SW1: SW_DIP_x01; SW_DIP_SPSTx01_Slide_9.78x4.72mm_W7.62mm_P2.54mm

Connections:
5V: K1.1, K2.1, K3.1, K4.1, K5.1, K6.1, K7.1, K8.1, K9.1, SW1.2
GND: D1.1 (K), D2.1 (K), D3.1 (K), D4.1 (K), D5.1 (K), D6.1 (K), D7.1 (K), D8.1 (K), D9.1 (K), J1.A1 (GND), J1.A12 (GND), J1.B1 (GND), J1.B12 (GND), J1.S1 (SHIELD), R10.1, R11.1
unnamed: D1.2 (A), R1.2
unnamed: D2.2 (A), R2.2
unnamed: D3.2 (A), R3.2
unnamed: D4.2 (A), R4.2
unnamed: D5.2 (A), R5.2
unnamed: D6.2 (A), R6.2
unnamed: D7.2 (A), R7.2
unnamed: D8.2 (A), R8.2
unnamed: D9.2 (A), R9.2
unnamed: J1.A5 (CC1), R10.2
unnamed: J1.B5 (CC2), R11.2
unnamed: K1.2, R1.1
unnamed: K2.2, R2.1
unnamed: K3.2, R3.1
unnamed: K4.2, R4.1
unnamed: K5.2, R5.1
unnamed: K6.2, R6.1
unnamed: K7.2, R7.1
unnamed: K8.2, R8.1
unnamed: K9.2, R9.1
VUSB: J1.A4 (VBUS), J1.A9 (VBUS), J1.B4 (VBUS), J1.B9 (VBUS), SW1.1

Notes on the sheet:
R1-9: At least 220 Ohms, higher resistance for less bright LEDs R10,11: 5.1 kOhms

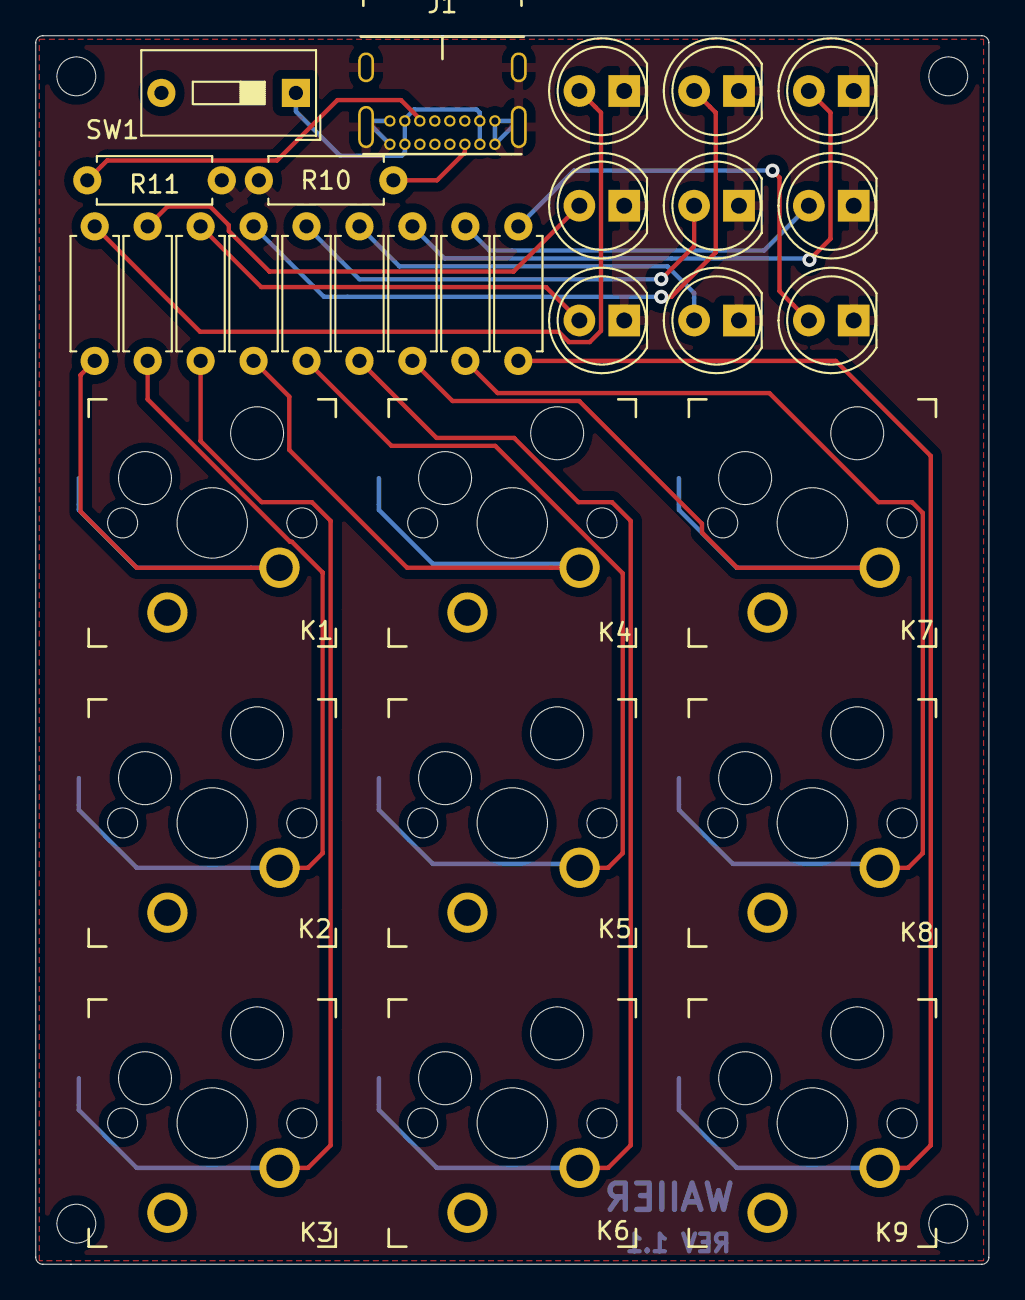
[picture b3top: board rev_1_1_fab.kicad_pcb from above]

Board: 2 copper layers, 54.0 x 69.6 mm, 31 parts (0 on the bottom side), 23 nets.

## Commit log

2020-10-02 add images on README
2020-10-02 up to routing section
2020-10-03 pcb instructions finished
2020-10-03 add parts ordering setcion
2020-10-03 add README.html to .gitignore
2020-10-10 rgb47 added
2020-10-11 switch testers
2020-11-02 long overdue update
